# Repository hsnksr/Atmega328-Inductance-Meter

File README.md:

# Atmega328-Inductance-Meter
This project is a modification project. This project has been done in order to measure and find near inductance value for basic power electronic application.This project has been developped for personal usege.Link of original project is "http://www.electronoobs.com/eng_arduino_tut10_3.php".

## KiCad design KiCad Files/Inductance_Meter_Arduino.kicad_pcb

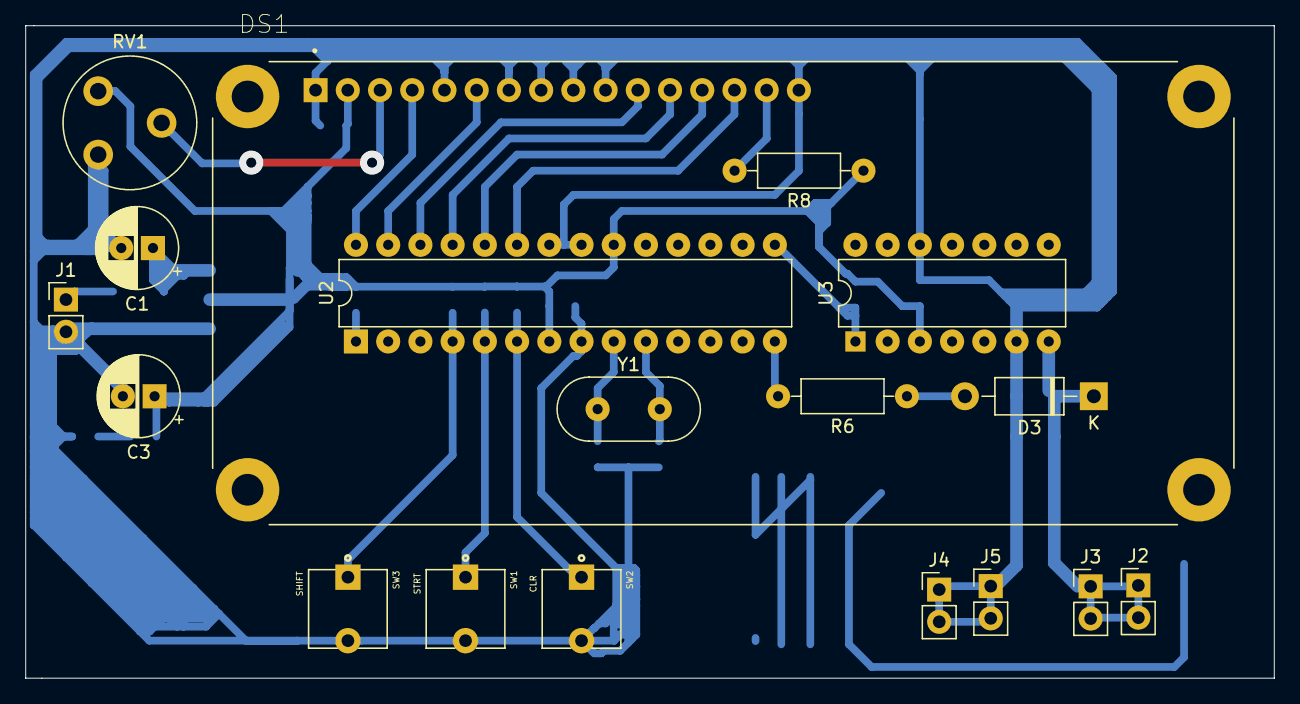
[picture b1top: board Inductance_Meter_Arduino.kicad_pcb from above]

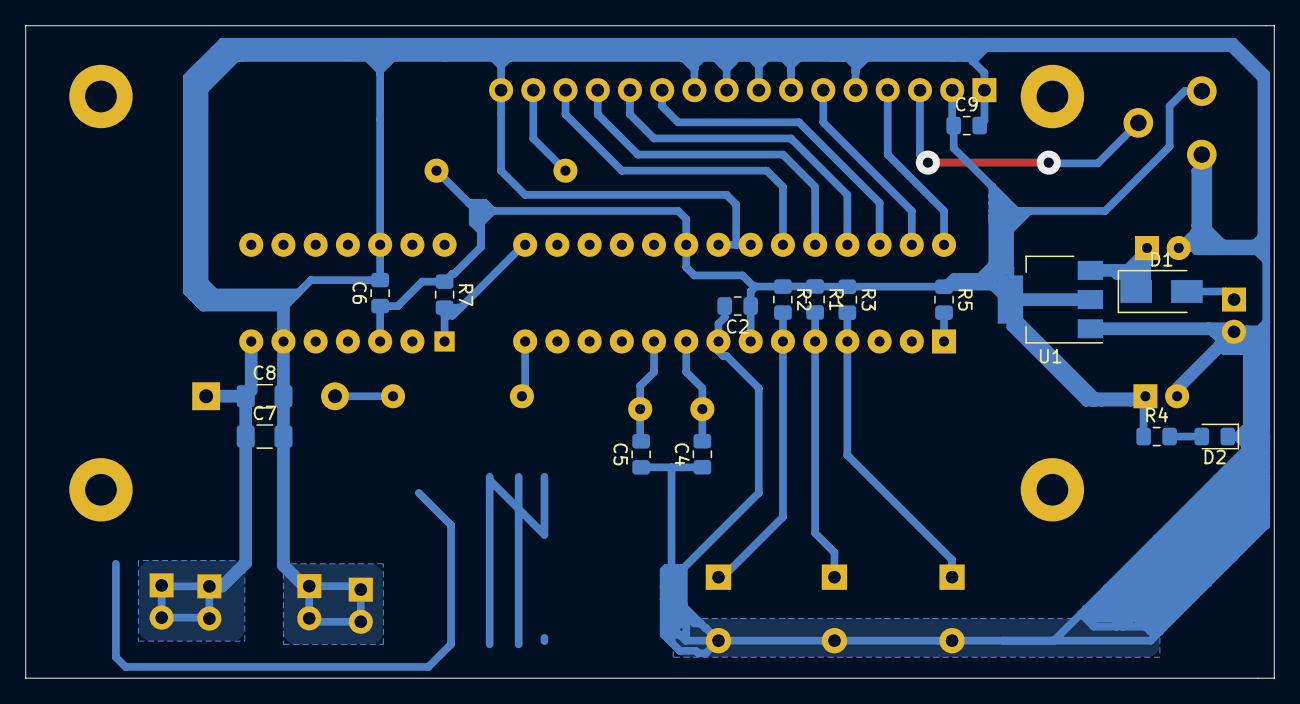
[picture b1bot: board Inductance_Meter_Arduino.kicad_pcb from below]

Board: 2 copper layers, 98.4 x 51.4 mm, 34 parts (16 on the bottom side), 23 nets.

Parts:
C1: 100uF; CP_Radial_D6.3mm_P2.50mm
C2, C6: 100nF; C_0805_2012Metric_Pad1.15x1.40mm_HandSolder
C3: 220uF; CP_Radial_D6.3mm_P2.50mm
C4, C5: 22pF; C_0805_2012Metric_Pad1.15x1.40mm_HandSolder
C7, C8: 1uF; C_1206_3216Metric_Pad1.42x1.75mm_HandSolder
C9: 470nF; C_0805_2012Metric_Pad1.15x1.40mm_HandSolder
D1: 1N4007; D_SMA
D2: LED-YLLW; LED_0805_2012Metric_Pad1.15x1.40mm_HandSolder
D3: 1N4007; D_DO-41_SOD81_P10.16mm_Horizontal
DS1: RC1602B-BIW-CSV; LCD_RC1602B-BIW-CSV
J1, J2, J3, J4, J5: Conn_01x02; PinHeader_1x02_P2.54mm_Vertical
R1, R2, R3, R5: 10k; R_0805_2012Metric_Pad1.15x1.40mm_HandSolder
R4: 1.5k; R_0805_2012Metric_Pad1.15x1.40mm_HandSolder
R6: 200; R_Axial_DIN0207_L6.3mm_D2.5mm_P10.16mm_Horizontal
R7: 1k; R_0805_2012Metric_Pad1.15x1.40mm_HandSolder
R8: 220; R_Axial_DIN0207_L6.3mm_D2.5mm_P10.16mm_Horizontal
RV1: R_POT_TRIM; Potentiometer_Piher_PT-10-V05_Vertical
SW1: STRT; SW_4-1437565-0
SW2: CLR; SW_4-1437565-0
SW3: SHIFT; SW_4-1437565-0
U1: LM1117-5.0; SOT-223-3_TabPin2
U2: ATmega328-PU; DIP-28_W7.62mm
U3: LM339; DIP-14_W7.62mm
Y1: 16MHz; Crystal_HC18-U_Vertical

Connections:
+5V: C2.1, C3.1, C6.1, C9.1, DS1.2, R1.1, R2.1, R3.1, R4.1, R5.1, R7.1, R8.1, RV1.3, U1.2, U2.7, U2.20, U3.3
CLEAR: R2.2, SW2.1, U2.6
DB4: DS1.11, U2.26
DB5: DS1.12, U2.25
DB6: DS1.13, U2.24
DB7: DS1.14, U2.23
EN: DS1.6, U2.27
GND: C1.2, C2.2, C3.2, C4.1, C5.1, C6.2, C7.2, C8.2, C9.2, D2.1, DS1.1, DS1.5, DS1.7, DS1.8, DS1.9, DS1.10, DS1.16, J1.2, J4.1, J4.2, J5.1, J5.2, RV1.1, SW1.2, SW2.2, SW3.2, U1.1, U2.8, U2.21, U2.22, U3.6, U3.12
unnamed: C1.1, D1.1, U1.3
unnamed: C4.2, U2.9, Y1.1
unnamed: C5.2, U2.10, Y1.2
unnamed: C7.1, C8.1, D3.1, J2.1, J2.2, J3.1, J3.2, U3.7
unnamed: D2.2, R4.2
unnamed: D3.2, R6.1
unnamed: DS1.3, RV1.2
unnamed: DS1.15, R8.2
unnamed: R5.2, U2.1
Pulse_In: R6.2, U2.14
Pulse_Out: R7.2, U2.15, U3.1
RS: DS1.4, U2.28
SHIFT: R3.2, SW3.1, U2.4
START: R1.2, SW1.1, U2.5
VCC: D1.2, J1.1

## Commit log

2020-02-29 Atmega328-Inductance-Meter
